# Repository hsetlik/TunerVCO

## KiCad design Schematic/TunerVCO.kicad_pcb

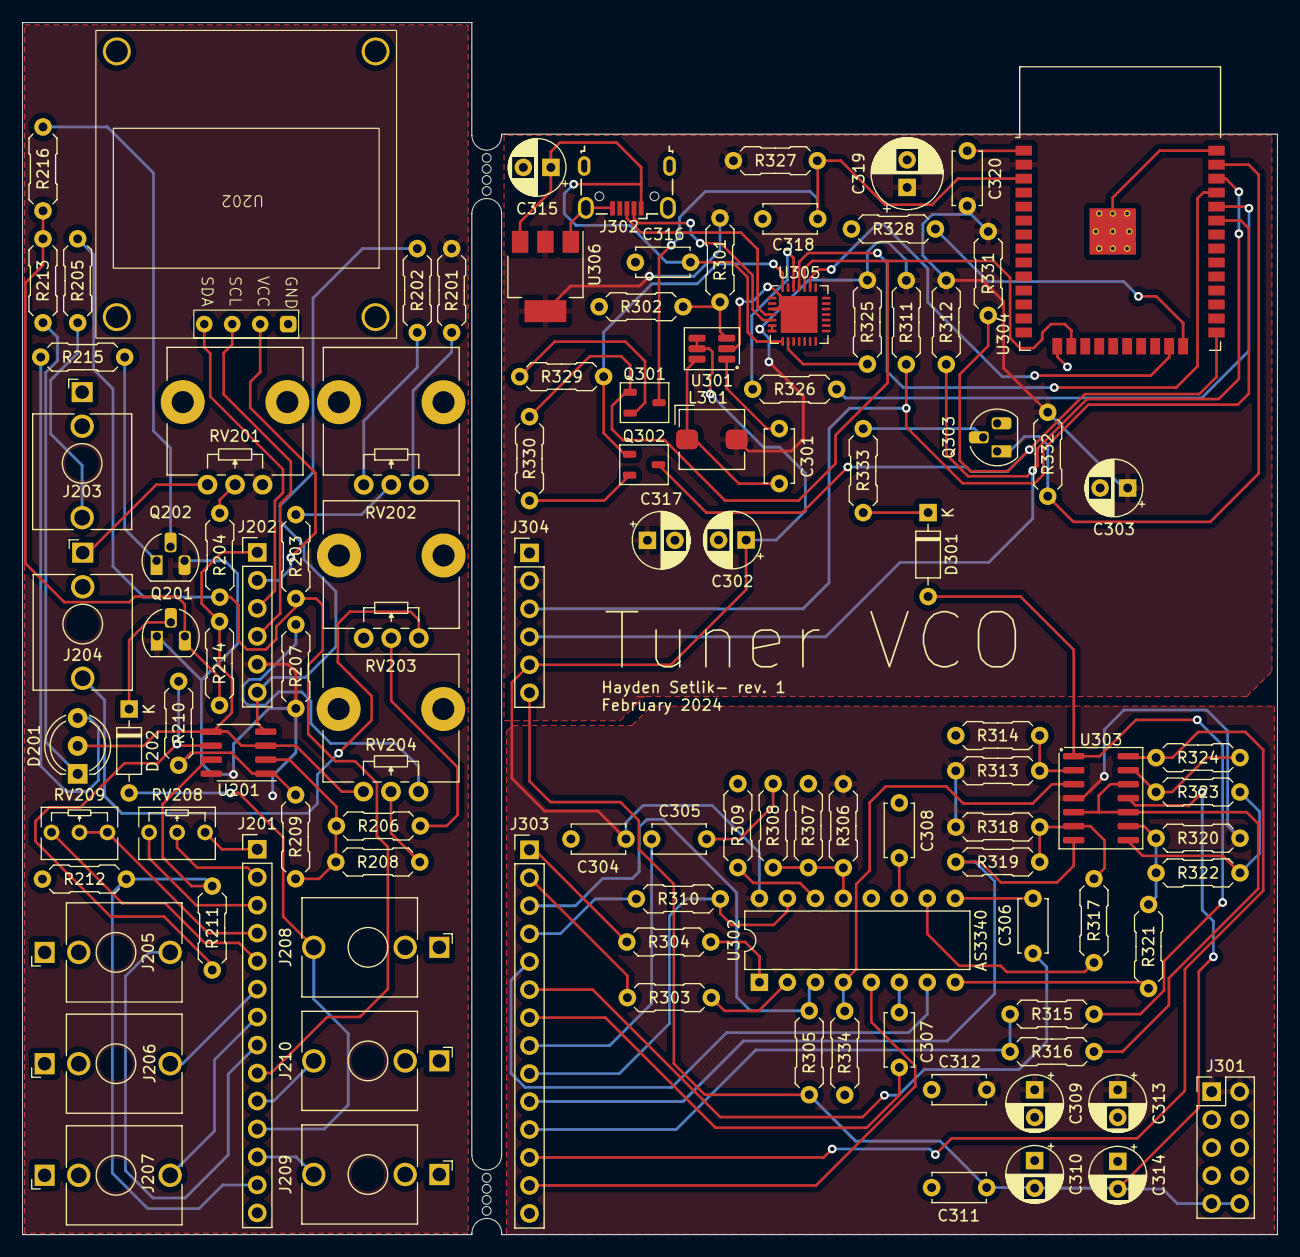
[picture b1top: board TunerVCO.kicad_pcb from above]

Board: 2 copper layers, 113.9 x 110.1 mm, 107 parts (0 on the bottom side), 94 nets.

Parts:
C301, C311, C312, C316: 0.1u; C_Disc_D4.7mm_W2.5mm_P5.00mm
C302, C303, C313, C314, C315, C317: 10uF; CP_Radial_D5.0mm_P2.50mm
C304, C305: 100n; C_Disc_D4.7mm_W2.5mm_P5.00mm
C306, C307, C308: 1n; C_Disc_D4.7mm_W2.5mm_P5.00mm
C309, C310: 33uF; CP_Radial_D5.0mm_P2.50mm
C318: 1nF; C_Disc_D4.7mm_W2.5mm_P5.00mm
C319: 100uF; CP_Radial_D6.3mm_P2.50mm
C320: 0.1uF; C_Disc_D4.7mm_W2.5mm_P5.00mm
D201: LED_Dual_AKA; LED_D5.0mm-3
D202, D301: 1N914; D_DO-35_SOD27_P7.62mm_Horizontal
J201, J303: LowerConn; PinHeader_1x14_P2.54mm_Vertical
J202, J304: UpperConn; PinHeader_1x06_P2.54mm_Vertical
J203: 1V/OCT; Jack_3.5mm_QingPu_WQP-PJ398SM_Vertical_CircularHoles
J204: PWM; Jack_3.5mm_QingPu_WQP-PJ398SM_Vertical_CircularHoles
J205: FM_T; Jack_3.5mm_QingPu_WQP-PJ398SM_Vertical_CircularHoles
J206: HARD SYNC; Jack_3.5mm_QingPu_WQP-PJ398SM_Vertical_CircularHoles
J207: SOFT SYNC; Jack_3.5mm_QingPu_WQP-PJ398SM_Vertical_CircularHoles
J208: Pulse; Jack_3.5mm_QingPu_WQP-PJ398SM_Vertical_CircularHoles
J209: Saw; Jack_3.5mm_QingPu_WQP-PJ398SM_Vertical_CircularHoles
J210: Triangle; Jack_3.5mm_QingPu_WQP-PJ398SM_Vertical_CircularHoles
J301: Conn_02x05_Odd_Even; PinHeader_2x05_P2.54mm_Vertical
J302: USB_B_Micro; USB_Micro-B_Wuerth_629105150521
L301: 4.7uH; L_Bourns_SRP5030T
Q201, Q303: BC547; TO-92_HandSolder
Q202: BC556; TO-92_HandSolder
Q301, Q302: S8050; TSOT-23
R201, R202: 680k; R_Axial_DIN0207_L6.3mm_D2.5mm_P7.62mm_Horizontal
R203, R204, R205, R206, R208, R209, R210, R211, R313, R314: 100k; R_Axial_DIN0207_L6.3mm_D2.5mm_P7.62mm_Horizontal
R207: 12k; R_Axial_DIN0207_L6.3mm_D2.5mm_P7.62mm_Horizontal
R212, R214, R311, R312, R325, R328, R331: 4k7; R_Axial_DIN0207_L6.3mm_D2.5mm_P7.62mm_Horizontal
R213, R215, R216, R315, R316, R333: 2k2; R_Axial_DIN0207_L6.3mm_D2.5mm_P7.62mm_Horizontal
R301: 51k; R_Axial_DIN0207_L6.3mm_D2.5mm_P7.62mm_Horizontal
R302: 22k; R_Axial_DIN0207_L6.3mm_D2.5mm_P7.62mm_Horizontal
R303: 5k6; R_Axial_DIN0207_L6.3mm_D2.5mm_P7.62mm_Horizontal
R304: 24k; R_Axial_DIN0207_L6.3mm_D2.5mm_P7.62mm_Horizontal
R305: 680; R_Axial_DIN0207_L6.3mm_D2.5mm_P7.62mm_Horizontal
R306: 1M5; R_Axial_DIN0207_L6.3mm_D2.5mm_P7.62mm_Horizontal
R307: 470; R_Axial_DIN0207_L6.3mm_D2.5mm_P7.62mm_Horizontal
R308, R310: 1M; R_Axial_DIN0207_L6.3mm_D2.5mm_P7.62mm_Horizontal
R309: 1k8; R_Axial_DIN0207_L6.3mm_D2.5mm_P7.62mm_Horizontal
R317, R334: 47k; R_Axial_DIN0207_L6.3mm_D2.5mm_P7.62mm_Horizontal
R318, R320: 220k; R_Axial_DIN0207_L6.3mm_D2.5mm_P7.62mm_Horizontal
R319, R321, R322: 92k; R_Axial_DIN0207_L6.3mm_D2.5mm_P7.62mm_Horizontal
R323, R324, R327, R329, R330, R332: 10k; R_Axial_DIN0207_L6.3mm_D2.5mm_P7.62mm_Horizontal
R326: 470R; R_Axial_DIN0207_L6.3mm_D2.5mm_P7.62mm_Horizontal
RV201: 10k Coarse; Potentiometer_Alps_RK09L_Single_Vertical
RV202: 10k Fine; Potentiometer_Alps_RK09L_Single_Vertical
RV203: 10k PWM Depth; Potentiometer_Alps_RK09L_Single_Vertical
RV204: 10k Pulse Width; Potentiometer_Alps_RK09L_Single_Vertical
RV208: 10k Trim1; Potentiometer_Bourns_3266Y_Vertical
RV209: 20k Trim2; Potentiometer_Bourns_3266Y_Vertical
U201: TL072; SOIC-8_3.9x4.9mm_P1.27mm
U202: SSD1306_OLED_128x64
U301: LMR50410; SOT-23-6_BigPads
U302: AS3340; DIP-16_W7.62mm
U303: TL074; SOIC-14_3.9x8.7mm_P1.27mm
U304: ESP32-WROOM-32
U305: CP2102N-Axx-xQFN28; QFN-28-1EP_5x5mm_P0.5mm_EP3.35x3.35mm
U306: AMS1117; SOT-223-3_TabPin2

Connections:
+3.3V: C303.1, C317.1, C319.1, C320.2, J304.2, L301.2, R301.1, R311.2, R312.2, R325.1, R327.1, R331.2, R332.2, U304.2 (VDD), U305.6 (VDD), U305.7 (VREGIN), U306.2 (VO)
+3.3VA: J202.2, U202.2 (VCC)
+12V: C302.1, C304.1, C309.1, C312.2, C313.1, J301.1, J301.2, J304.5, R306.2, R313.1, R318.1, R320.1, U301.4 (EN), U301.5 (VIN), U302.16 (VCC), U303.4 (V+)
+12VA: J202.5, Q201.1 (C), Q202.3 (E), R201.1, R207.2, RV201.1, U201.8 (V+)
-12V: C310.2, C311.1, C314.2, J301.9, J301.10, J304.6, R305.1, U303.11 (V-)
-12VA: J202.6, R202.2, U201.4 (V-)
CTS: U304.23 (IO15), U305.23 (~CTS)
DTR: Q302.1 (E), R329.1, U305.28 (~DTR)
EN: C318.2, Q301.3 (C), R327.2, U304.3 (EN)
FM: C305.1, J303.8
FM_T: J201.8, J205.T
GND: C302.2, C303.2, C304.2, C308.1, C309.2, C310.1, C311.2, C312.1, C313.2, C314.1, C315.2, C316.1, C317.2, C318.1, C319.2, C320.1, J301.3, J301.4, J301.5, J301.6, J301.7, J301.8, J302.5 (GND), J302.6 (Shield), J303.14, J304.1, Q303.3 (E), R302.2, R307.1, R309.1, R314.2, R316.2, R328.2, R334.2, U301.2 (GND), U302.12 (Gnd), U303.5 (+), U303.10 (+), U303.12 (+), U304.1 (GND), U304.15 (GND), U304.38 (GND), U304.39 (GND), U305.3 (GND), U305.29 (GND), U306.1 (ADJ)
GNDA: D201.2 (K), J201.14, J202.1, J203.S, J204.S, J205.S, J206.S, J207.S, J208.S, J209.S, J210.S, R212.1, R214.2, RV201.3, RV203.3, RV204.3, U201.3 (+), U201.5 (+), U202.1 (GND)
HS: C306.1, J303.6
HS_T: J201.6, J206.T
IO0: Q302.3 (C), R331.1, U304.25 (IO0)
unnamed: C305.2, R308.2
unnamed: D201.1 (A1), R213.2
unnamed: D201.3 (A2), R215.2
unnamed: D202.1 (K), Q201.2 (B)
unnamed: D301.1 (K), R333.1
unnamed: J203.T, R205.1
unnamed: J204.T, RV203.1
unnamed: J302.3 (D+), U305.4 (D+)
unnamed: J302.2 (D-), U305.5 (D-)
unnamed: Q201.3 (E), R213.1, R214.1, R216.2
unnamed: Q202.2 (B), R216.1
unnamed: Q202.1 (C), R215.1
unnamed: Q301.2 (B), R329.2
unnamed: Q302.2 (B), R330.2
unnamed: Q303.2 (B), R333.2
unnamed: Q303.1 (C), R332.1, U304.37 (IO23)
unnamed: R201.2, RV202.1
unnamed: R202.1, RV202.3
unnamed: R203.1, RV202.2
unnamed: R204.1, RV201.2
unnamed: R206.1, RV203.2
unnamed: R207.1, RV204.1
unnamed: R208.1, RV204.2
unnamed: R209.2, R210.1, U201.1
unnamed: R322.2, R323.1, U303.8
unnamed: R206.2, R208.2, R209.1, U201.2 (-)
unnamed: R210.2, R211.1, U201.6 (-)
unnamed: C301.1, U301.1 (CB)
unnamed: R301.2, R302.1, U301.3 (FB)
unnamed: C301.2, L301.1, U301.6 (SW)
unnamed: C306.2, U302.9 (HSync)
unnamed: R306.1, R307.2, R308.1, U302.13 (LinFM)
unnamed: R334.1, U302.4 (PULSE), U303.3 (+)
unnamed: R321.1, U302.8 (SAW)
unnamed: R304.2, U302.1 (SCALE1)
unnamed: R303.2, U302.2 (SCALE2)
unnamed: C307.2, U302.6 (SSync)
unnamed: R309.2, U302.14 (Scale)
unnamed: C308.2, U302.11 (TCAP)
unnamed: R317.1, U302.10 (TRI)
unnamed: R313.2, R314.1, U303.2 (-)
unnamed: R317.2, R318.2, R319.1, U303.6 (-)
unnamed: R320.2, R321.2, R322.1, U303.9 (-)
unnamed: R323.2, R324.1, U303.13 (-)
unnamed: R328.1, U304.24 (IO2)
unnamed: R326.1, U305.26 (TXD)
unnamed: R325.2, U305.9 (~RST)
PITCH_CV: J303.9, R310.1, U302.15 (CV)
PITCH_CV_T: J201.9, R203.2, R204.2, R205.2
PULSE_HI: D301.2 (A), R315.1, U303.1
PULSE_OUT: J303.11, R315.2, R316.1
PULSE_OUT_T: D202.2 (A), J201.11, J208.T
PWM_CV: J303.13, U302.5 (PWM)
PWM_CV_T: J201.13, R211.2, R212.2, U201.7
RTS: Q301.1 (E), R330.1, U304.16 (IO13), U305.24 (~RTS)
RXD0: R326.2, U304.34 (RXD0/IO3)
SAW_OUT: J303.12, R324.2, U303.14
SAW_OUT_T: J201.12, J209.T
SCL: J304.4, R312.1, U304.36 (IO22)
SCL_T: J202.4, U202.3 (SCL)
SDA: J304.3, R311.1, U304.33 (IO21)
SDA_T: J202.3, U202.4 (SDA)
SS: C307.1, J303.7
SS_T: J201.7, J207.T
T1A: J303.1, R304.1
T1A_T: J201.1, RV208.1
T1B: J303.2, R303.1
T1B_T: J201.2, RV208.2
T1C: J303.3, R305.2, U302.3 (VEE)
T1C_T: J201.3, RV208.3
T2B: J303.4, R310.2
T2B_T: J201.4, RV209.1, RV209.2
T2C: J303.5, U302.7 (HFTrack)
T2C_T: J201.5, RV209.3
TRI_OUT: J303.10, R319.2, U303.7
TRI_OUT_T: J201.10, J210.T
TXD0: U304.35 (TXD0/IO1), U305.25 (RXD)
VBUS: C315.1, C316.2, J302.1 (VBUS), U305.8 (VBUS), U306.3 (VI)

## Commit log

2024-02-15 tuning and display logic
2024-02-15 tested on hardware- getting accurate hz readings
2024-02-15 fully operational :)
2024-02-15 new font
2024-02-15 added KiCad stuff to git
2024-02-15 more responsive buffer, added hz readout
2024-02-15 schematic PDF
